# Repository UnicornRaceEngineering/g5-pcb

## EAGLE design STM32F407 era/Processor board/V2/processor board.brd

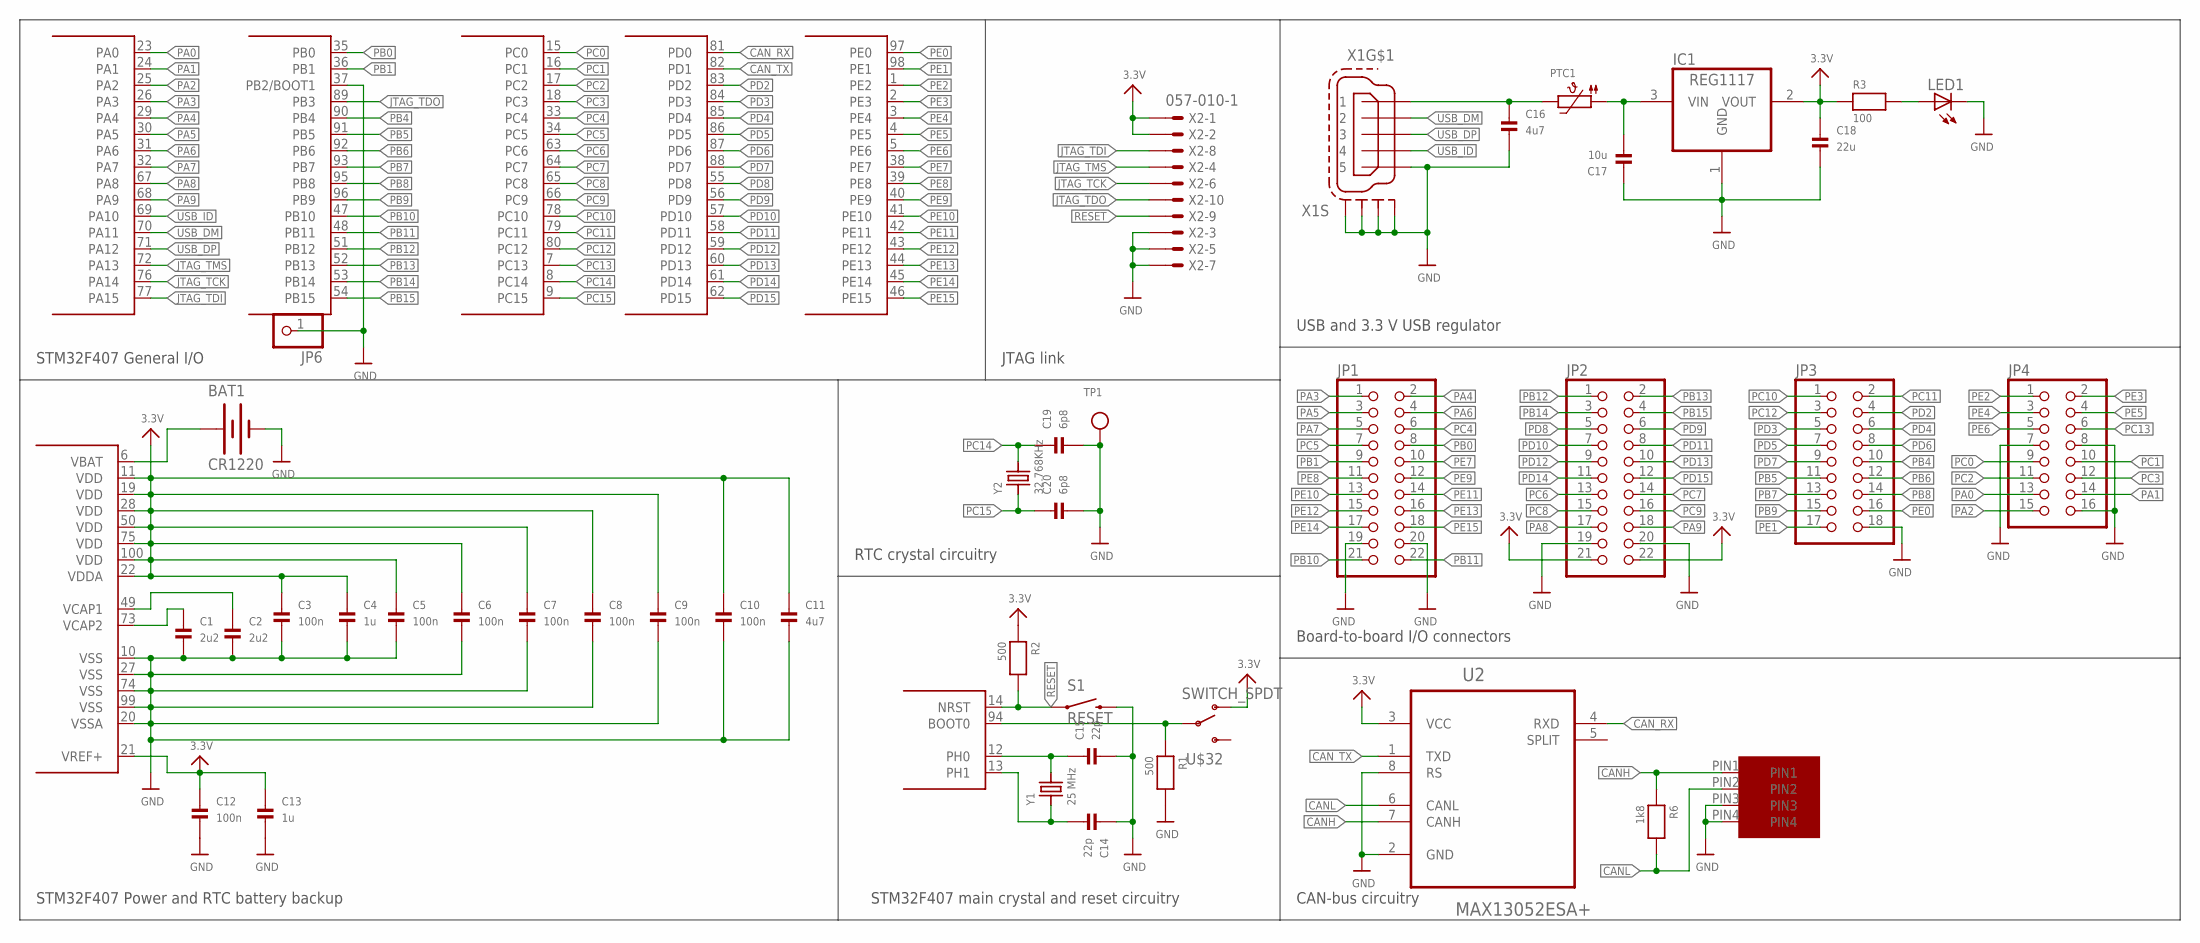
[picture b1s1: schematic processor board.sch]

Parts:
BAT1: CR1220; BATTCON_12MM_PTH
C1, C2: 2u2; _0603MP
C3, C5, C6, C7, C8, C9, C10, C12: 100n; _0603MP
C4, C13: 1u; _0603MP
C11, C16: 4u7; _0603MP
C14, C15: 22p; _0603MP
C17: 10u; _0603MP
C18: 22u; _0603MP
C19, C20: 6p8; _0603MP
IC1: REG1117; SOT223
JP1, JP2: PINHD-2X11; 2X11
JP3: PINHD-2X9; 2X09
JP4: PINHD-2X8; 2X08
JP6: PINHD-1X1; 1X01
LED1: LEDCHIPLED_1206; CHIPLED_1206
PTC1: PTC1206; 1206
R1, R2: 500; _0603MP
R3: 100; _0603MP
R6: 1k8; _0603MP
S1: RESET; TACTILE-SWITCH-1101NE
TP1: TESTPOINT0.1"; 1X01_ROUND
U1: STM32F4-100; SQFP-S-14X14-100
U2: MAX13052ESA+; SOIC127P600X175-8N
U$23: MICROFIT4; MICROFIT4SOCK
U$32: SWITCH_SPDT; KPS-1290
X1: MINI-USB-SCHIELD-32005-201; 32005-201
X2: 057-010-1
Y1: 25 MHz; CRYSTAL_2.5X2
Y2: 32.768KHz; CRYSTAL_CYL_2X6MM_SMT

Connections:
3.3V: C3.1, C4.1, C5.1, C6.1, C7.1, C8.1, C9.1, C10.1, C11.1, C12.1, C13.1, C18.1, IC1.2 (VOUT), JP2.21, JP2.22, R2.1, R3.1, U1.11 (VDD), U1.19 (VDD), U1.21 (VREF+), U1.22 (VDDA), U1.28 (VDD), U1.50 (VDD), U1.75 (VDD), U1.100 (VDD), U2.3 (VCC), U$32.O, X2.1, X2.2
CANH: R6.1, U2.7 (CANH), U$23.PIN1; also elsewhere on the board
CANL: R6.2, U2.6 (CANL), U$23.PIN2; also elsewhere on the board
CAN_RX: U1.81 (PD0), U2.4 (RXD)
CAN_TX: U1.82 (PD1), U2.1 (TXD)
GND: BAT1.GND (-), C1.2, C2.2, C3.2, C4.2, C5.2, C6.2, C7.2, C8.2, C9.2, C10.2, C11.2, C12.2, C13.2, C14.1, C15.2, C16.2, C17.1, C18.2, C19.2, C20.2, IC1.1 (GND), JP1.19, JP1.20, JP2.19, JP2.20, JP3.18, JP4.7, JP4.8, JP4.16, JP6.1, LED1.C, R1.2, S1.2, TP1.1, U1.10 (VSS), U1.20 (VSSA), U1.27 (VSS), U1.37 (PB2/BOOT1), U1.74 (VSS), U1.99 (VSS), U2.2 (GND), U2.8 (RS), U$23.PIN3, U$23.PIN4, X1.5, X1.M1 (S1), X1.M2 (S2), X1.M3 (S3), X1.M4 (S4), X2.3, X2.5, X2.7; also elsewhere on the board
JTAG_TCK: U1.76 (PA14), X2.6
JTAG_TDI: U1.77 (PA15), X2.8
JTAG_TDO: U1.89 (PB3), X2.10
JTAG_TMS: U1.72 (PA13), X2.4
unnamed: C15.1, U1.12 (PH0), Y1.3 (2)
unnamed: C1.1, U1.73 (VCAP2)
unnamed: C2.1, U1.49 (VCAP1)
unnamed: R1.1, U1.94 (BOOT0), U$32.P
unnamed: LED1.A, R3.2
unnamed: BAT1.VCC@1 (+), U1.6 (VBAT)
unnamed: C17.2, IC1.3 (VIN), PTC1.1
unnamed 17: U2.5 (SPLIT); also elsewhere on the board
unnamed: C14.2, U1.13 (PH1), Y1.1
PA0: JP4.13, U1.23 (PA0)
PA1: JP4.14, U1.24 (PA1)
PA2: JP4.15, U1.25 (PA2)
PA3: JP1.1, U1.26 (PA3)
PA4: JP1.2, U1.29 (PA4)
PA5: JP1.3, U1.30 (PA5)
PA6: JP1.4, U1.31 (PA6)
PA7: JP1.5, U1.32 (PA7)
PA8: JP2.17, U1.67 (PA8)
PA9: JP2.18, U1.68 (PA9)
PB0: JP1.8, U1.35 (PB0)
PB1: JP1.9, U1.36 (PB1)
PB4: JP3.10, U1.90 (PB4)
PB5: JP3.11, U1.91 (PB5)
PB6: JP3.12, U1.92 (PB6)
PB7: JP3.13, U1.93 (PB7)
PB8: JP3.14, U1.95 (PB8)
PB9: JP3.15, U1.96 (PB9)
PB10: JP1.21, U1.47 (PB10)
PB11: JP1.22, U1.48 (PB11)
PB12: JP2.1, U1.51 (PB12)
PB13: JP2.2, U1.52 (PB13)
PB14: JP2.3, U1.53 (PB14)
PB15: JP2.4, U1.54 (PB15)
PC0: JP4.9, U1.15 (PC0)
PC1: JP4.10, U1.16 (PC1)
PC2: JP4.11, U1.17 (PC2)
PC3: JP4.12, U1.18 (PC3)
PC4: JP1.6, U1.33 (PC4)
PC5: JP1.7, U1.34 (PC5)
PC6: JP2.13, U1.63 (PC6)
PC7: JP2.14, U1.64 (PC7)
PC8: JP2.15, U1.65 (PC8)
PC9: JP2.16, U1.66 (PC9)
PC10: JP3.1, U1.78 (PC10)
PC11: JP3.2, U1.79 (PC11)
PC12: JP3.3, U1.80 (PC12)
PC13: JP4.6, U1.7 (PC13)
PC14: C19.1, U1.8 (PC14), Y2.2
PC15: C20.1, U1.9 (PC15), Y2.1
PD2: JP3.4, U1.83 (PD2)
PD3: JP3.5, U1.84 (PD3)
PD4: JP3.6, U1.85 (PD4)
PD5: JP3.7, U1.86 (PD5)
PD6: JP3.8, U1.87 (PD6)
PD7: JP3.9, U1.88 (PD7)
PD8: JP2.5, U1.55 (PD8)
PD9: JP2.6, U1.56 (PD9)
PD10: JP2.7, U1.57 (PD10)
PD11: JP2.8, U1.58 (PD11)
PD12: JP2.9, U1.59 (PD12)
PD13: JP2.10, U1.60 (PD13)
PD14: JP2.11, U1.61 (PD14)
PD15: JP2.12, U1.62 (PD15)
PE0: JP3.16, U1.97 (PE0)
PE1: JP3.17, U1.98 (PE1)
PE2: JP4.1, U1.1 (PE2)
PE3: JP4.2, U1.2 (PE3)
PE4: JP4.3, U1.3 (PE4)
PE5: JP4.4, U1.4 (PE5)
PE6: JP4.5, U1.5 (PE6)
PE7: JP1.10, U1.38 (PE7)
PE8: JP1.11, U1.39 (PE8)
PE9: JP1.12, U1.40 (PE9)
PE10: JP1.13, U1.41 (PE10)
PE11: JP1.14, U1.42 (PE11)
PE12: JP1.15, U1.43 (PE12)
PE13: JP1.16, U1.44 (PE13)
PE14: JP1.17, U1.45 (PE14)
PE15: JP1.18, U1.46 (PE15)
RESET: R2.2, S1.1, U1.14 (NRST), X2.9
USB_DM: U1.70 (PA11), X1.2
USB_DP: U1.71 (PA12), X1.3
USB_ID: U1.69 (PA10), X1.4
USB_VBUS: C16.1, PTC1.2, X1.1

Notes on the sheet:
STM32F407 Power and RTC battery backup
STM32F407 main crystal and reset circuitry
RTC crystal circuitry
STM32F407 General I/O
JTAG link
USB and 3.3 V USB regulator
CAN-bus circuitry
Board-to-board I/O connectors

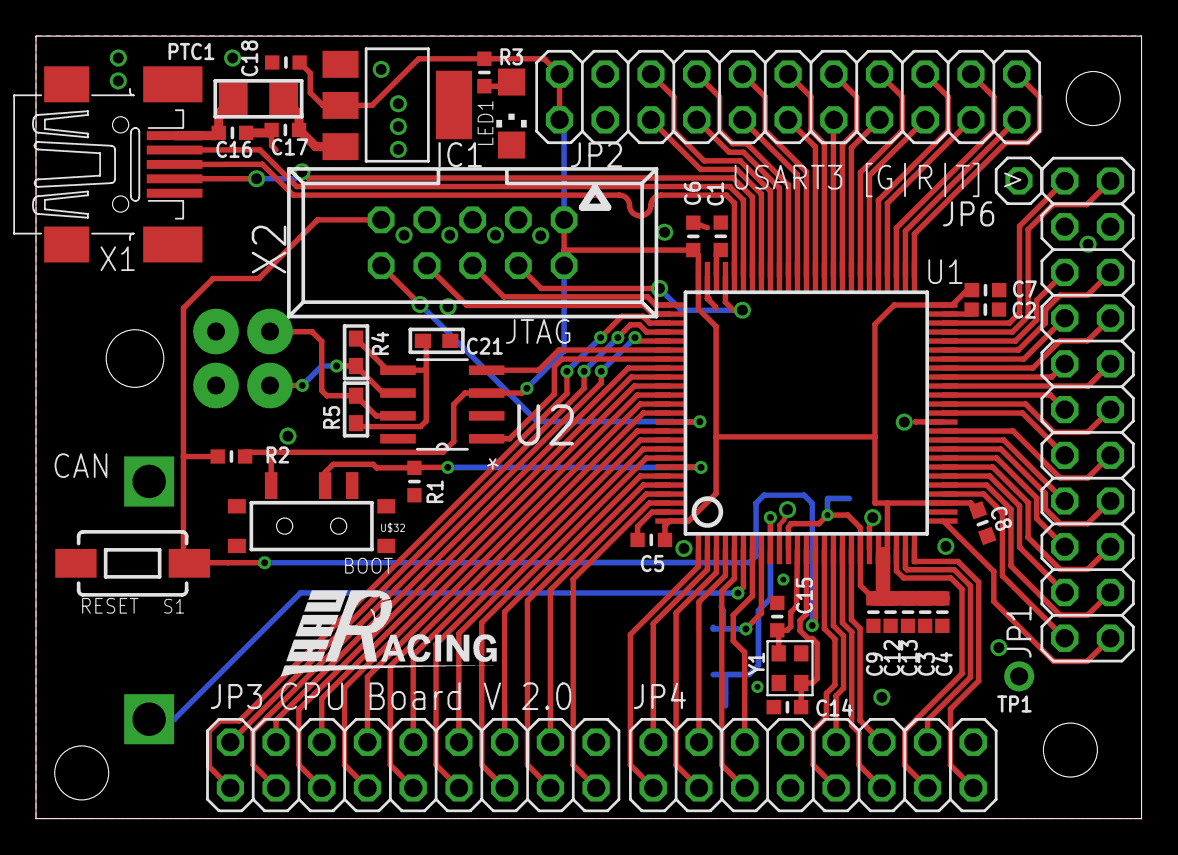
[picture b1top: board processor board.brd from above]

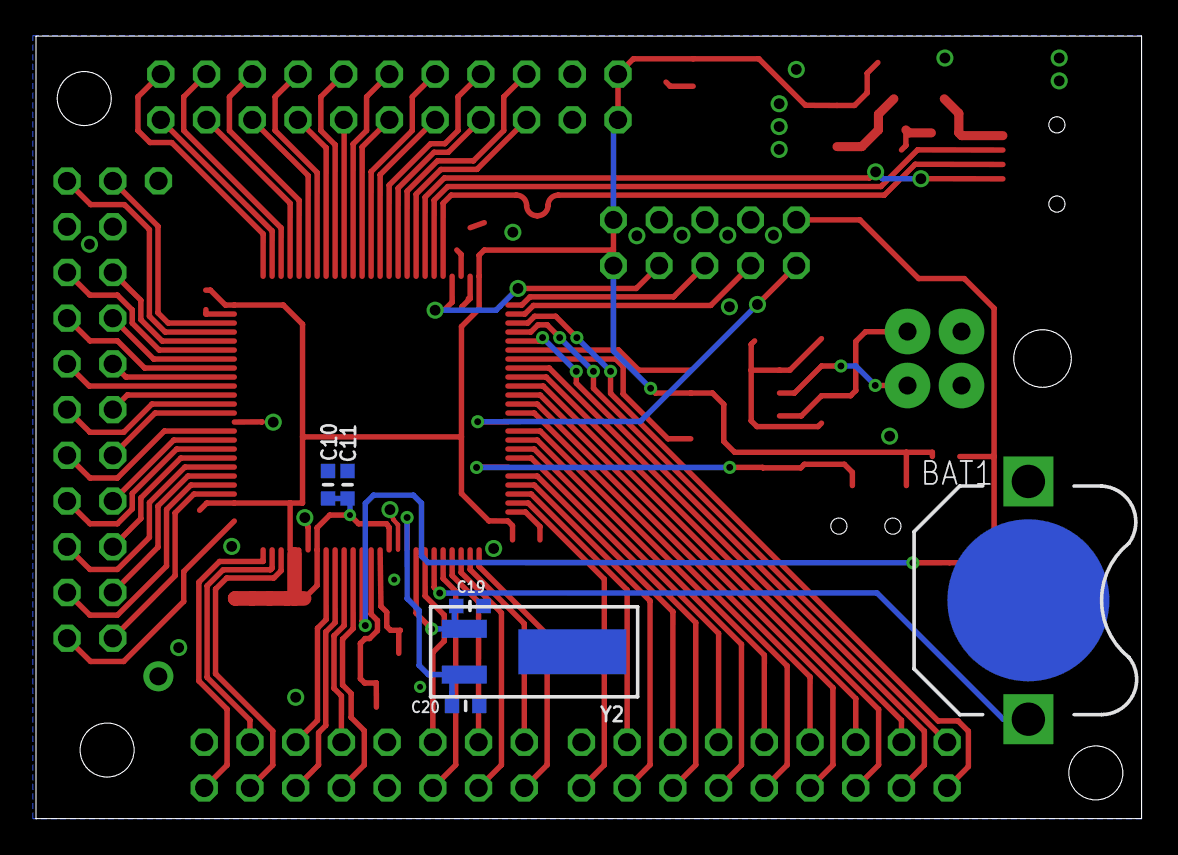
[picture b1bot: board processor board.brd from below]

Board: 2 copper layers, 61.4 x 43.5 mm, 45 parts (6 on the bottom side), 94 nets.

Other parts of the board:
C21: 4n7; _0603
R4, R5: 60; _0603

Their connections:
CANH: R5.2; also elsewhere on the board
CANL: R4.2; also elsewhere on the board
GND: C21.1; also elsewhere on the board
unnamed 17: C21.2, R4.1, R5.1; also elsewhere on the board

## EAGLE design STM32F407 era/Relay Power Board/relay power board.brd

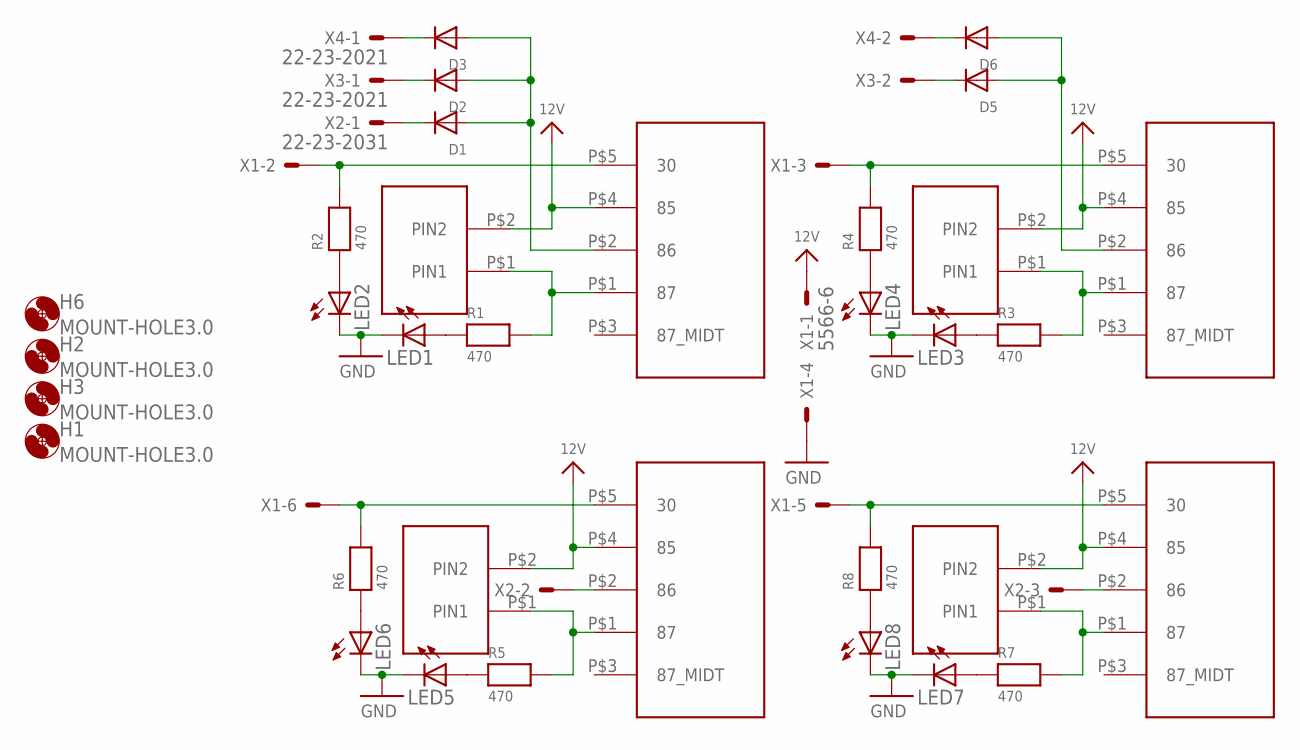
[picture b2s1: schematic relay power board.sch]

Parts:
D1, D2, D3, D5, D6: DIODESMA; SMADIODE
H1, H2, H3, H6: MOUNT-HOLE3.0; 3,0
LED1, LED2, LED3, LED4, LED5, LED6, LED7, LED8: LEDCHIPLED_1206; CHIPLED_1206
R1, R2, R3, R4, R5, R6, R7, R8: 470; _0603
U$1, U$2, U$4, U$10: FUSE_SOCKET; FUSE_SOCKET_12V_30A
U$3, U$5, U$11, U$18: LITTE_FUSE; LITTE_FUSE_PAC
X1: 5566-6
X2: 22-23-2031
X3, X4: 22-23-2021

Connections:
12V: U$1.P$4 (85), U$2.P$4 (85), U$3.P$2 (PIN2), U$4.P$4 (85), U$5.P$2 (PIN2), U$10.P$4 (85), U$11.P$2 (PIN2), U$18.P$2 (PIN2), X1.1
GND: LED1.C, LED2.C, LED3.C, LED4.C, LED5.C, LED6.C, LED7.C, LED8.C, X1.4
unnamed: R3.2, U$2.P$1 (87), U$3.P$1 (PIN1)
unnamed: R1.2, U$1.P$1 (87), U$5.P$1 (PIN1)
unnamed: D1.A, D2.A, D3.A, U$1.P$2 (86)
unnamed: LED1.A, R1.1
unnamed: LED2.A, R2.1
unnamed: R2.2, U$1.P$5 (30), X1.2
unnamed: D5.A, D6.A, U$2.P$2 (86)
unnamed: LED3.A, R3.1
unnamed: LED4.A, R4.1
unnamed: R4.2, U$2.P$5 (30), X1.3
unnamed: R5.2, U$10.P$1 (87), U$11.P$1 (PIN1)
unnamed: R7.2, U$4.P$1 (87), U$18.P$1 (PIN1)
unnamed: LED5.A, R5.1
unnamed: LED6.A, R6.1
unnamed: R6.2, U$10.P$5 (30), X1.6
unnamed: U$10.P$2 (86), X2.2
unnamed: LED7.A, R7.1
unnamed: LED8.A, R8.1
unnamed: R8.2, U$4.P$5 (30), X1.5
unnamed: U$4.P$2 (86), X2.3
unnamed: D1.C, X2.1
unnamed: D2.C, X3.1
unnamed: D5.C, X3.2
unnamed: D3.C, X4.1
unnamed: D6.C, X4.2

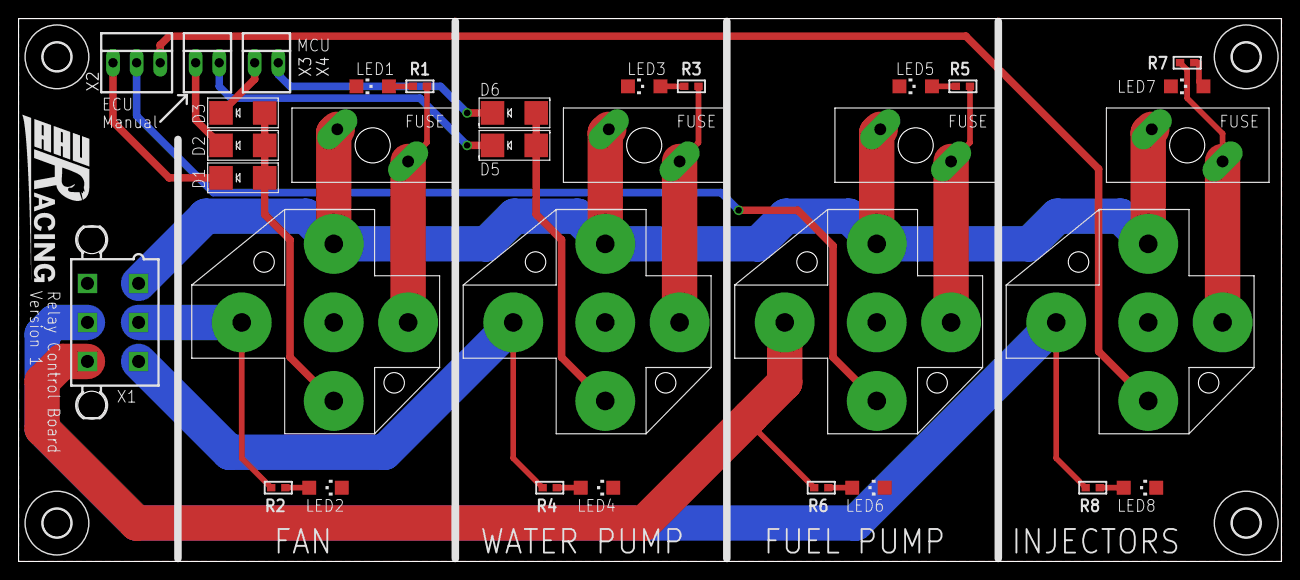
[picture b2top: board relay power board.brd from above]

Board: 2 copper layers, 135.9 x 58.4 mm, 37 parts (0 on the bottom side), 27 nets.

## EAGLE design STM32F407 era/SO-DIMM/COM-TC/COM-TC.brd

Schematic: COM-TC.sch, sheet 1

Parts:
C1, C6, C8, C9, C10, C11, C12, C13, C14, C18, C19, C20, C21, C22, C23, C24, C25, C26, C27, C28, C29, C30, C31, C38, C39, C40, C45, C50: 100n; _0603
C2, C42: 4,7u; _0805
C3, C7, C32, C33, C43, C44: 10n; _0603
C4: SUPERCAP
C15, C34, C35, C36, C37, C46: 1n; _0603
C16, C47: 47p; _0603
C17, C41, C48, C49: 47u; _0805
CN1: USBMINIBLARGE; USB-MINIB_LARGER
D1, D3: DIODESOD-323F; SOD-323F
D2, D8: BA340A; SMA-DIODE
H1, H2, H3, H4, H5, H6: MOUNT-HOLE3.0; 3,0
J1, J2: CON1; AUTOCONNECTOR
J3: SO-DIMM-CPU; SODIMM-CONNECTOR-2.5V
J4: FTDI_DEVICE; FTDI_DEVICE_SIDE
JTAG1: JTAG-ARM
L1, L2: SRN6045TA-680M; INDUCTOR_6X6MM_TDK_VLC6045
PTC2: PTC1812
Q1, Q2, Q3, Q11: TRANSISTOR_NPNWIDE; SOT23-WIDE
R1, R67: 332k; _0603
R2, R70: 68k1; _0603
R4, R6, R30, R54, R56, R58: 499; _0603
R5, R8, R31, R55, R57, R59: 976; _0603
R9, R10, R17, R24, R25, R32, R63, R64, R65: 500; _0603
R11, R14: 120; _0603
R12, R13, R15, R19, R22, R33, R34, R35, R36, R37, R38, R60, R61, R62: 10k; _0603
R16, R18, R20, R21, R23: 4k7; _0603
R26: 60; _0603
R27, R39, R41, R42, R48, R49, R51, R52: 10k 0W5; _0805
R40, R43, R50, R53: RESISTOR_0805; _0805
R44, R45, R46, R47: 1k; _0603
R66, R71: 29k4; _0603
R68, R72: 10k2; _0603
R69: 3k24; _0603
R73: 1k91; _0603
S1, S2, S3, S4: SWITCH-SPDT-SMD-A; SWITCH-SPST-SMD-A
SW1: SWITCH_DPDT; DPDT_SMT_JS202011SCQN
U1: IRF9332PBF; SOIC127P600X175-8N
U2: MAX232AEWE+; SOIC127P1032X265-16N
U3, U7: TPS54331D; SOIC127P600X175-8N
U4: TXB0108PWR; TSSOP20
U5, U6: MAX9926; SOP63P600X175-16N
U8: MCP3004-I/ST; SOP65P640X120-14N
U9: AD5024BRUZ; SOP65P640X120-16N
U10: SN65HVD232D; SOIC127P600X175-8N
U11: LTC3112EFEPBF; SOP65P640X120-20N
U$1: SDMMC06132; 06132
U$19, U$24, U$30, U$33, U$34, U$37, U$39, U$40, U$43, U$45, U$47, U$49, U$55, U$57, U$59: MCP6001T-E/OT; SOT95P270X145-5N
X1: 057-014-1
XB1: XBEE-PRO

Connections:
3.3V: C6.2, C10.2, C17.1, C18.2, C19.2, C20.2, C21.2, C22.2, C23.2, C24.2, C25.2, C26.2, C27.2, C28.2, C29.2, C30.2, C31.2, C40.1, C41.1, C50.1, J1.D3 (D), J1.D4 (D), J1.G4 (G), J2.H4 (H), J2.J4 (J), J2.K1 (K), J2.K2 (K), J2.K3 (K), J2.K4 (K), J3.197 (VCC), J3.199 (VCC), JTAG1.1, JTAG1.2, L1.P$2 (2), R12.1, R13.1, R15.1, R16.1, R18.1, R19.1, R20.1, R21.1, R22.1, R23.1, R24.1, R25.1, R32.1, R33.2, R34.2, R35.1, R36.1, R37.1, R38.1, R60.1, R61.1, R62.1, R68.1, U2.16 (VCC), U4.2 (VCCA), U4.10 (OE), U8.13 (VREF), U8.14 (VDD), U10.3 (VCC), U$1.4 (VDD), U$19.5 (VDD), U$24.5 (VDD), U$30.5 (VDD), U$33.5 (VDD), U$34.5 (VDD), U$37.5 (VDD), U$39.5 (VDD), U$40.5 (VDD), U$43.5 (VDD), U$45.5 (VDD), U$47.5 (VDD), U$49.5 (VDD), U$55.5 (VDD), U$57.5 (VDD), U$59.5 (VDD), X1.2, XB1.1 (VCC)
5.0V: C1.2, C13.1, C38.1, C39.1, C48.1, C49.1, L2.P$2 (2), R44.2, R45.2, R46.2, R47.2, R63.1, R64.1, R65.1, R72.1, U4.19 (VCCB), U5.14 (VCC), U6.14 (VCC), U9.3 (VDD), U9.4 (VREFB), U9.5 (VREFA), U9.9 (VREFC), U9.11 (VREFD), X1.1
12V: C2.1, C3.1, C42.1, C43.1, J1.A4 (A), PTC2.P$1 (1), R1.1, R67.1, U3.2 (VIN), U7.2 (VIN), X1.3
ADC_CS: U8.8 (*CS/SHDN)
AUX2: J1.E1 (E), S2.2
AUX2I: R60.2, S2.1 (O)
AUX3: J1.E2 (E), S3.2
AUX3I: R61.2, S3.1 (O)
AUX4: J1.E3 (E), S4.2
AUX4I: R62.2, S4.1 (O)
AUX5: J1.E4 (E)
AUX6: J2.E1 (E)
AUX7: J2.E3 (E)
BITE: J1.A1 (A), Q11.3 (C), R65.2
BITEL: Q11.2 (E)
BRAKE-POT: J1.C3 (C), U$57.3 (VIN+)
BRAKE-POTB: U$57.1 (VOUT), U$57.4 (VIN-)
BRAKEP: J2.F4 (F), R19.2, U$39.3 (VIN+)
BRAKEP2: J2.F2 (F), R15.2, U$43.3 (VIN+)
BRAKEP2B: U$43.1 (VOUT), U$43.4 (VIN-)
BRAKEPB: U$39.1 (VOUT), U$39.4 (VIN-)
CANH: J2.D2 (D), SW1.P$5 (P2), U10.7 (CANH), X1.7
CANL: J2.D1 (D), SW1.P$2 (P1), U10.6 (CANL), X1.8
CAN_RX: J3.93 (PD0), U10.4 (R)
CAN_TX: J3.95 (PD1), U10.1 (D)
CLUTCH-POT: J1.C4 (C), U$59.3 (VIN+)
CLUTCH-POTB: U$59.1 (VOUT), U$59.4 (VIN-)
COMRX: U2.9 (R2OUT)
COMTX: U2.10 (T2IN)
DACCLR: U9.10 (CLR*)
DACCS: U9.2 (SYNC*)
DBG_RX: J4.P$3 (RXI), X1.6
DBG_TX: J4.P$2 (TXO), X1.5
ECU1: J2.C4 (C), Q1.3 (C), R64.2
ECU1L: Q1.2 (E)
ECU2: J2.D4 (D), Q2.3 (C), R63.2
ECU2L: Q2.2 (E)
ENCODER1: C32.1, J1.G2 (G), R35.2
ENCODER2: C33.1, J1.G3 (G), R36.2
FUELTEMP: J1.C2 (C), R22.2, U$55.3 (VIN+)
FUELTEMPB: U$55.1 (VOUT), U$55.4 (VIN-)
GEARPOSAN: J2.H3 (H), U$49.3 (VIN+)
GEARPOSANB: U$49.1 (VOUT), U$49.4 (VIN-)
GND: C1.1, C2.2, C3.2, C4.P$3, C6.1, C7.2, C10.1, C11.2, C12.1, C13.2, C16.2, C17.2, C18.1, C19.1, C20.1, C21.1, C22.1, C23.1, C24.1, C25.1, C26.1, C27.1, C28.1, C29.1, C30.1, C31.1, C32.2, C33.2, C38.2, C39.2, C40.2, C41.2, C42.2, C43.2, C44.2, C47.2, C48.2, C49.2, C50.2, CN1.GND, D2.A, D8.A, J1.B1 (B), J1.B2 (B), J1.B3 (B), J1.B4 (B), J1.D2 (D), J1.F1 (F), J1.F2 (F), J1.F3 (F), J1.F4 (F), J1.G1 (G), J1.H4 (H), J1.J1 (J), J1.M4 (M), J2.C3 (C), J2.D3 (D), J2.E2 (E), J2.E4 (E), J2.G1 (G), J2.G2 (G), J2.G3 (G), J2.G4 (G), J2.H2 (H), J2.J2 (J), J2.M1 (M), J2.M2 (M), J2.M3 (M), J2.M4 (M), J3.2 (GND), J3.4 (GND), J3.6 (GND), J3.8 (GND), J3.10 (GND), J3.12 (GND), J3.14 (GND), J3.16 (GND), J3.18 (GND), J3.20 (GND), J3.22 (GND), J3.24 (GND), J3.26 (GND), J3.28 (GND), J3.30 (GND), J3.32 (GND), J3.34 (GND), J3.36 (GND), J3.38 (GND), J3.40 (GND), J3.42 (GND), J3.44 (GND), J3.46 (GND), J3.48 (GND), J3.50 (GND), J3.52 (GND), J3.54 (GND), J3.56 (GND), J3.58 (GND), J3.60 (GND), J3.62 (GND), J3.64 (GND), J3.66 (GND), J3.68 (GND), J3.70 (GND), J3.77 (GND), J3.78 (GND), J3.79 (GND), J3.80 (GND), J3.81 (GND), J3.83 (GND), J3.85 (GND), J3.92 (GND), J3.94 (GND), J3.96 (GND), J3.98 (GND), J3.100 (GND), J3.102 (GND), J3.104 (GND), J3.106 (GND), J3.108 (GND), J3.110 (GND), J3.112 (GND), J3.114 (GND), J3.116 (GND), J3.118 (GND), J3.120 (GND), J3.122 (GND), J3.124 (GND), J3.125 (GND), J3.126 (GND), J3.127 (GND), J3.128 (GND), J3.129 (GND), J3.130 (GND), J3.131 (GND), J3.132 (GND), J3.134 (GND), J3.136 (GND), J3.138 (GND), J3.140 (GND), J3.142 (GND), J3.144 (GND), J3.146 (GND), J3.148 (GND), J3.150 (GND), J3.152 (GND), J3.154 (GND), J3.156 (GND), J3.158 (GND), J3.159 (GND), J3.160 (GND), J3.161 (GND), J3.162 (GND), J3.163 (GND), J3.164 (GND), J3.165 (GND), J3.166 (GND), J3.167 (GND), J3.168 (GND), J3.169 (GND), J3.170 (GND), J3.171 (GND), J3.172 (GND), J3.173 (GND), J3.174 (GND), J3.175 (GND), J3.176 (GND), J3.177 (GND), J3.178 (GND), J3.179 (GND), J3.180 (GND), J3.181 (GND), J3.182 (GND), J3.183 (GND), J3.184 (GND), J3.185 (GND), J3.186 (GND), J3.187 (GND), J3.188 (GND), J3.189 (GND), J3.190 (GND), J3.191 (GND), J3.192 (GND), J3.193 (GND), J3.194 (GND), J3.195 (GND), J3.196 (GND), J3.198 (GND), J3.200 (GND), J4.P$6 (GND), JTAG1.3, JTAG1.4, JTAG1.6, JTAG1.8, JTAG1.10, JTAG1.12, JTAG1.14, JTAG1.16, JTAG1.18, JTAG1.20, Q3.2 (E), R2.2, R5.1, R8.1, R31.1, R55.1, R57.1, R59.1, R66.2, R69.2, R70.2, R71.2, R73.2, U1.4 (G), U2.15 (GND), U3.7 (GND), U4.11 (GND), U5.1 (IN_THRS1), U5.3 (BIAS), U5.6 (BIAS2), U5.8 (INT_THRS2), U5.11 (GND), U5.13 (OUT1), U6.1 (IN_THRS1), U6.3 (BIAS), U6.6 (BIAS2), U6.8 (INT_THRS2), U6.11 (GND), U6.13 (OUT1), U7.7 (GND), U8.7 (DGND), U8.12 (AGND), U9.1 (LDAC*), U9.8 (POR), U9.14 (GND), U10.2 (GND), U$1.3 (VSS1), U$1.6 (VSS2), U$1.GP (GND), U$19.2 (VSS), U$24.2 (VSS), U$30.2 (VSS), U$33.2 (VSS), U$34.2 (VSS), U$37.2 (VSS), U$39.2 (VSS), U$40.2 (VSS), U$43.2 (VSS), U$45.2 (VSS), U$47.2 (VSS), U$49.2 (VSS), U$55.2 (VSS), U$57.2 (VSS), U$59.2 (VSS), X1.4, X1.14, XB1.10 (GND)
GND-RELAY: D1.A, D3.A, J1.K1 (K), R9.2, R10.2
GSENS: J1.A2 (A), R4.2
GSENSO: R33.1, U$24.1 (VOUT), U$24.4 (VIN-)
HB1-DIR: U4.6 (A5)
HB1-DIR-IN: J1.J4 (J), U4.15 (B5)
HB1-EN: U4.7 (A6)
HB1-EN-IN: J1.H1 (H), U4.14 (B6)
HB1-PWM: U4.5 (A4)
HB1-PWM-IN: J1.J3 (J), U4.16 (B4)
HB2-DIR: U4.3 (A2)
HB2-DIR-IN: J1.K4 (K), U4.18 (B2)
HB2-EN: U4.1 (A1)
HB2-EN-IN: J1.K3 (K), U4.20 (B1)
HB2-PWM: U4.4 (A3)
HB2-PWM-IN: J1.J2 (J), U4.17 (B3)
IGNCUT: R17.2
IGNCUTO: J2.H1 (H), Q3.3 (C)
JTAG_TCK: J3.84 (TCK), JTAG1.9
JTAG_TDI: J3.86 (TDI), JTAG1.5
JTAG_TDO: J3.88 (TDO), JTAG1.13
JTAG_TMS: J3.82 (TMS), JTAG1.7
MISO: U8.10 (DOUT), X1.12
MOSI: U8.9 (DIN), U9.15 (DIN), X1.11
unnamed: C7.1, U3.4 (SS)
unnamed: R1.2, R2.1, U3.3 (EN)
unnamed: Q11.1 (B), R32.2
unnamed: R26.2, SW1.P$4 (S2)
unnamed: R4.1, R5.2, U$24.3 (VIN+)
unnamed: R26.1, SW1.P$3 (S1)
unnamed: C34.1, R27.2, R40.2, U5.16 (IN1+)
unnamed: PTC2.P$2 (2), U1.5 (D_4), U1.6 (D), U1.7 (D_2), U1.8 (D_3)
unnamed: C12.2, U2.6 (V-)
unnamed: C9.1, U2.4 (C2+)
unnamed: C34.2, R39.2, R40.1, U5.15 (IN1-)
unnamed: C35.1, R41.2, R43.2, U5.9 (IN2+)
unnamed: C35.2, R42.2, R43.1, U5.10 (IN2-)
unnamed: C9.2, U2.5 (C2-)
unnamed: C8.2, U2.3 (C1-)
unnamed: C8.1, U2.1 (C1+)
unnamed: C11.1, U2.2 (V+)
unnamed: Q3.1 (B), R17.1
unnamed: R44.1, U5.5 (COUT2)
unnamed: R46.1, U6.5 (COUT2)
unnamed: R30.2, S2.3 (S)
unnamed: R45.1, U5.4 (COUT1)
unnamed: R6.1, R8.2, U$19.3 (VIN+)
unnamed: R47.1, U6.4 (COUT1)
unnamed: Q1.1 (B), R24.2
unnamed: Q2.1 (B), R25.2
unnamed: C36.1, R48.2, R50.2, U6.16 (IN1+)
unnamed: C14.2, U3.1 (BOOT)
unnamed: C37.1, R51.2, R53.2, U6.9 (IN2+)
unnamed: C37.2, R52.2, R53.1, U6.10 (IN2-)
unnamed: C36.2, R49.2, R50.1, U6.15 (IN1-)
unnamed: R54.1, R55.2, U8.1 (CH0)
unnamed: R30.1, R31.2, U8.2 (CH1)
unnamed: C14.1, D2.C, L1.P$1 (1), U3.8 (PH)
unnamed: R56.2, S3.3 (S)
unnamed: C15.2, R66.1
unnamed: R56.1, R57.2, U8.3 (CH2)
unnamed: C44.1, U7.4 (SS)
unnamed: R54.2, S1.3 (S)
unnamed: R58.2, S4.3 (S)
unnamed: R58.1, R59.2, U8.4 (CH3)
unnamed: C15.1, C16.1, U3.6 (COMP)
unnamed: R67.2, R70.1, U7.3 (EN)
unnamed: R68.2, R69.1, U3.5 (VSENSE)
unnamed: C45.2, U7.1 (BOOT)
unnamed: C45.1, D8.C, L2.P$1 (1), U7.8 (PH)
unnamed: C46.2, R71.1
unnamed: C46.1, C47.1, U7.6 (COMP)
unnamed: R72.2, R73.1, U7.5 (VSENSE)
unnamed: CN1.ID, J3.72 (ID)
NEUTRAL: J2.J1 (J), R37.2
OC1: R11.2
OC2: R14.2
OILP: J1.C1 (C), S1.2
OILPI: R38.2, S1.1 (O)
RESET: J3.90 (RESET), JTAG1.15
RLY1: D1.C, J1.L1 (L)
RLY2: D3.C, J1.M1 (M)
RLY3: J1.L2 (L)
RLY4: J1.M2 (M)
RLY5: J1.L3 (L)
RLY6: J1.M3 (M)
RPM1GIN: J2.B4 (B), R42.1
RPM1IN: J2.A4 (A), R41.1
RPM2GIN: J2.B3 (B), R27.1
RPM2IN: J2.A3 (A), R39.1
RPM3GIN: J2.B2 (B), R52.1
RPM3IN: J2.A2 (A), R51.1
RPM4GIN: J2.B1 (B), R48.1
RPM4IN: J2.A1 (A), R49.1
RS232RX: J2.C1 (C), U2.8 (R2IN)
RS232TX: J2.C2 (C), U2.7 (T2OUT)
SCK: U8.11 (CLK), U9.16 (SCLK), X1.13
SCL: X1.10
SDA: X1.9
SDIO_CMD: J3.97 (PD2), R16.2, U$1.2 (DATA_IN)
SDIO_D0: J3.69 (PC8), R23.2, U$1.7 (DATA_OUT)
SDIO_D1: J3.71 (PC9), R20.2, U$1.8 (DAT1)
SDIO_D2: J3.87 (PC10), R21.2, U$1.9 (DAT2)
SDIO_D3: J3.89 (PC11), R18.2, U$1.1 (CS)
SDIO_SCK: J3.91 (PC12), U$1.5 (SCLK)
SD_IN: J3.73 (PA8)
SPEED: J2.J3 (J), U$33.3 (VIN+)
SPEEDB: U$33.1 (VOUT), U$33.4 (VIN-)
TRAVEL1: J2.L3 (L), U$30.3 (VIN+)
TRAVEL1B: U$30.1 (VOUT), U$30.4 (VIN-)
TRAVEL2: J2.L4 (L), U$34.3 (VIN+)
TRAVEL2B: U$34.1 (VOUT), U$34.4 (VIN-)
TRAVEL3: J2.L2 (L), U$37.3 (VIN+)
TRAVEL3B: U$37.1 (VOUT), U$37.4 (VIN-)
TRAVEL4: J2.L1 (L), U$40.3 (VIN+)
TRAVEL4B: U$40.1 (VOUT), U$40.4 (VIN-)
VBUS: CN1.VBUS
VCC: J1.L4 (L), U1.1 (S_2), U1.2 (S), U1.3 (S_3)
VOUT: J1.H3 (H), U9.6 (VOUTA)
VTEMP: J2.F1 (F), R13.2, U$45.3 (VIN+)
VTEMP2: J2.F3 (F), R12.2, U$47.3 (VIN+)
VTEMP2B: U$47.1 (VOUT), U$47.4 (VIN-)
VTEMPB: U$45.1 (VOUT), U$45.4 (VIN-)
YAW: J1.A3 (A), R6.2
YAWO: R34.1, U$19.1 (VOUT), U$19.4 (VIN-)
_N: CN1.D-, J3.74 (D-)
_P: CN1.D+, J3.76 (D+)

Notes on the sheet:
CPU Board
RS232 Transciever
CAN Transciever
5V to 3,3V
Ignition cut
DAC
Power protection
Mounting Holes
ECU AUX 1
ECU AUX 2
Wheel Speed triggers
Main Connector 1
Main Connector 2
Relay control (Relay box)
BITE
Travel Sensor buffers
SD-Card
Header and mounting holes
3,3V Power supply
5V Power supply
JTAG
FTDI Debug UART
Debug header

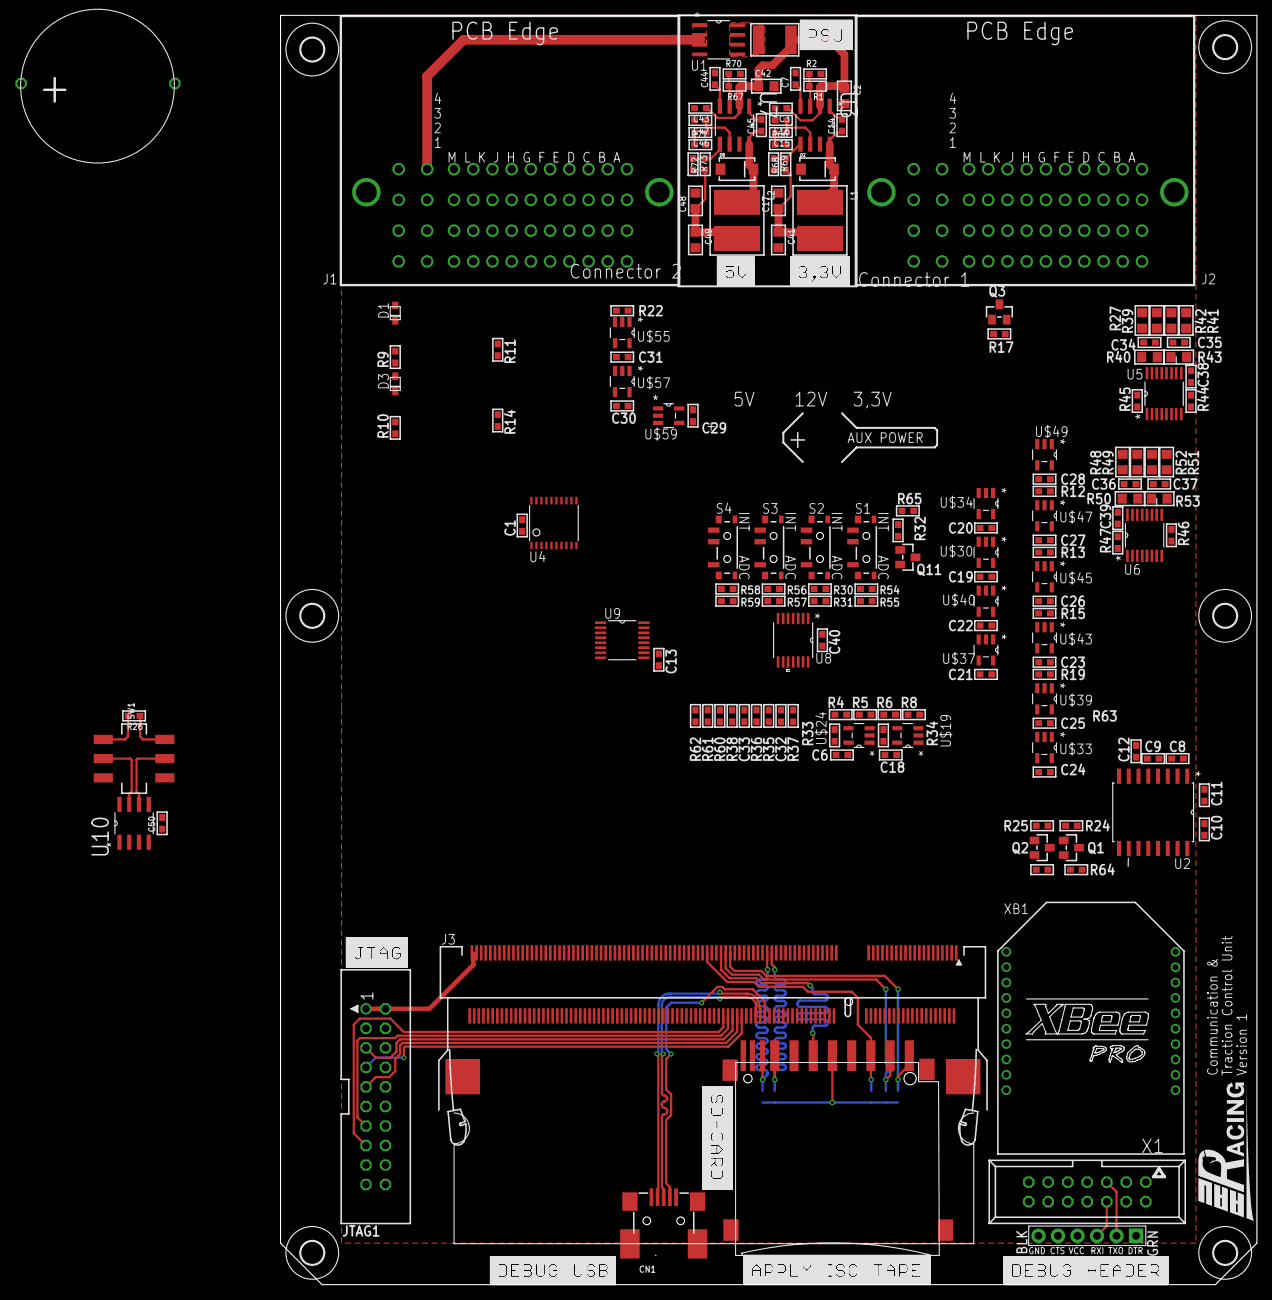
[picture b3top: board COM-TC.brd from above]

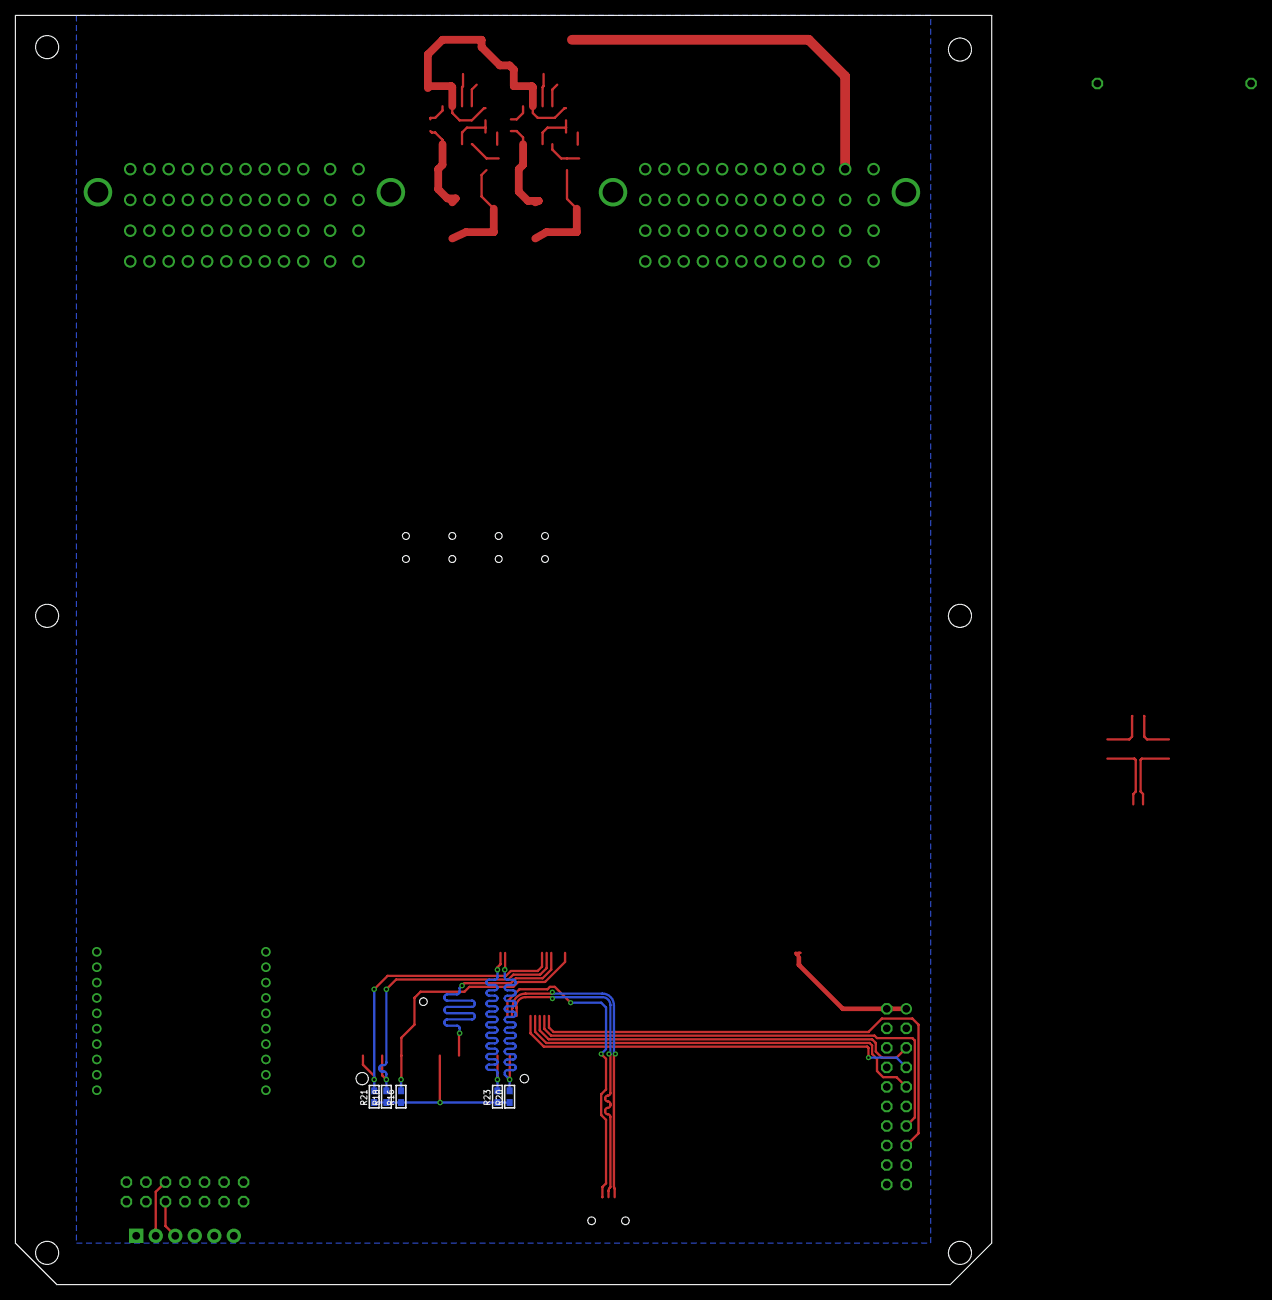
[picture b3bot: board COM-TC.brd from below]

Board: 2 copper layers, 127.0 x 165.1 mm, 174 parts (5 on the bottom side), 142 nets.

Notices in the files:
parts and their libraries:
microbuilder: This work is placed in the public domain, and may be freely used for commercial and non-commercial work with the following conditions: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
SparkFun-Electromechanical: Licensing: Creative Commons ShareAlike 4.0 International - https://creativecommons.org/licenses/by-sa/4.0
